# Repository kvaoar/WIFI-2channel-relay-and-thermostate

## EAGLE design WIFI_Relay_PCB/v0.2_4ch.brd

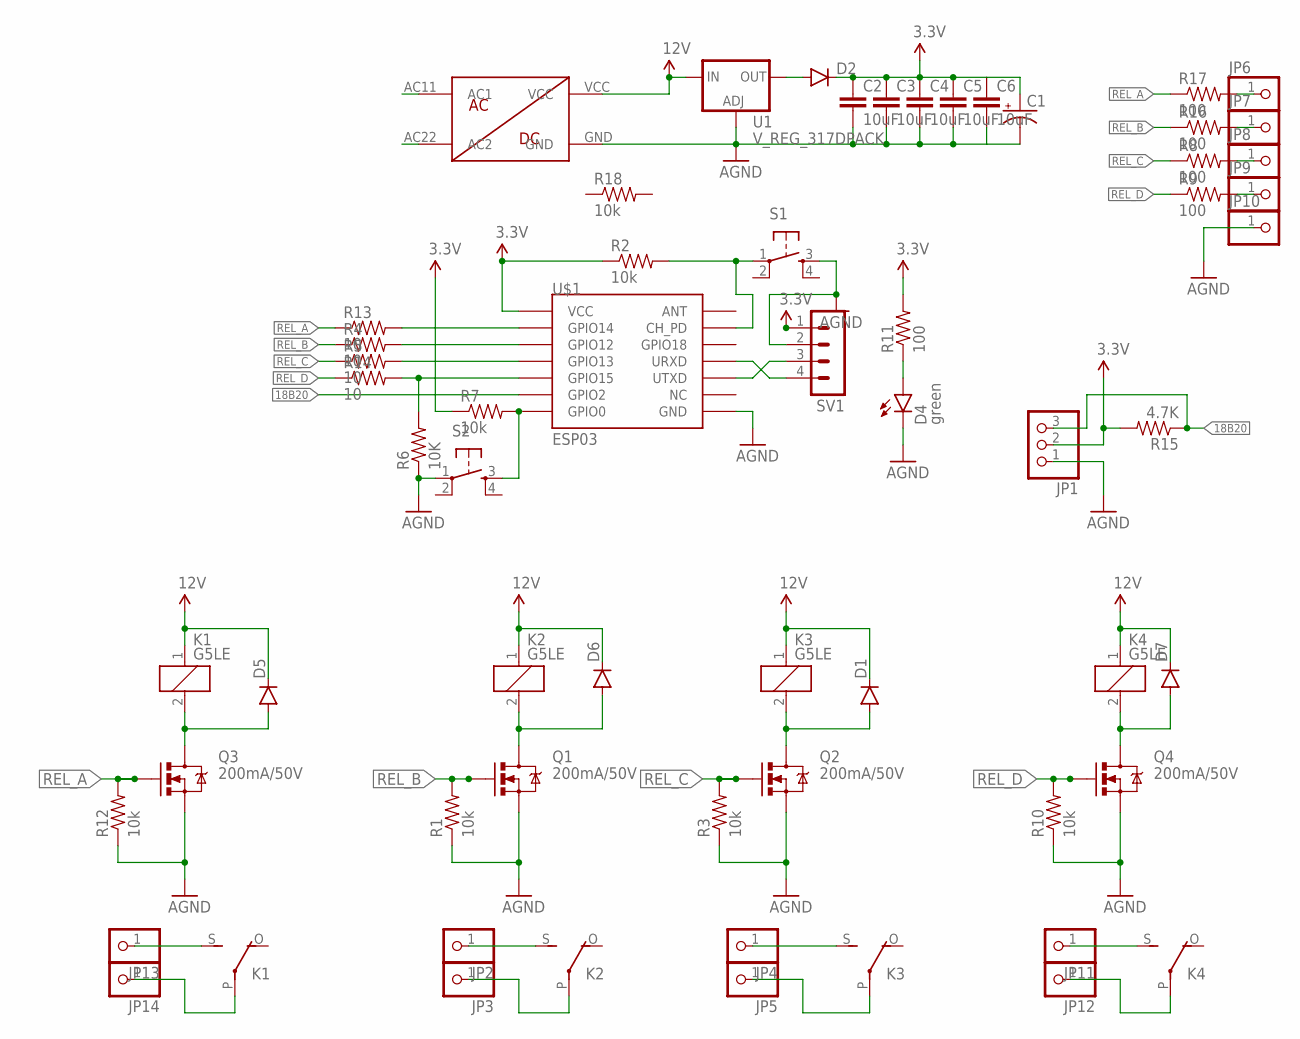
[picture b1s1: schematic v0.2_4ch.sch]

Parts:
C1: CAP_POLPTH3; CPOL-RADIAL-1000UF-63V
C2, C3, C4, C5, C6: 10uF; 0603-CAP
D1, D2, D5, D6, D7: DIODESOD123; SOD-123
D4: green; LED-0603
JP1: PINHD-1X3; 1X03
JP2, JP3, JP4, JP5, JP6, JP7, JP8, JP9, JP10, JP11, JP12, JP13, JP14: PINHD-1X1; 1X01
K1, K2, K3, K4: G5LE
Q1, Q2, Q3, Q4: 200mA/50V; SOT23-3
R1, R2, R3, R7, R10, R12, R18: 10k; 0805
R4, R5, R13, R14: 10; 0805
R6: 10K; 0805
R8, R9, R11, R16, R17: 100; 0805
R15: 4.7K; 0805
S1, S2: TAC_SWITCHPTH; TACTILE-PTH
SV1: MA04-1
U1: V_REG_317DPACK; V-REG_DPACK
U$1: ESP03
U$8: ACDC12V350MA

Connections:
3.3V: C1.1 (+), C2.1, C3.1, C4.1, C5.1, C6.1, D2.C, JP1.2, R2.1, R7.1, R11.2, R15.2, SV1.1, U$1.VCC
12V: D1.C, D5.C, D6.C, D7.C, K1.1, K2.1, K3.1, K4.1, U1.3 (IN), U$8.VCC
18B20: JP1.3, R15.1, U$1.GPIO2
AGND: C1.2 (-), C2.2, C3.2, C4.2, C5.2, C6.2, D4.C, JP1.1, JP10.1, Q1.2 (S), Q2.2 (S), Q3.2 (S), Q4.2 (S), R1.1, R3.1, R6.1, R10.1, R12.1, S1.3, S2.1, SV1.2, U1.1 (ADJ), U$1.GND, U$8.GND
unnamed: SV1.3, U$1.UTXD
unnamed: SV1.4, U$1.URXD
unnamed: D5.A, K1.2, Q3.3 (D)
unnamed: R2.2, S1.1, U$1.CH_PD
unnamed: R4.2, U$1.GPIO12
unnamed: R5.2, U$1.GPIO13
unnamed: R6.2, R14.2, U$1.GPIO15
unnamed: JP8.1, R8.2
unnamed: JP9.1, R9.2
unnamed: R7.2, S2.3, U$1.GPIO0
unnamed: D4.A, R11.1
unnamed: D6.A, K2.2, Q1.3 (D)
unnamed: D7.A, K4.2, Q4.3 (D)
unnamed: D1.A, K3.2, Q2.3 (D)
unnamed: R13.2, U$1.GPIO14
unnamed: JP13.1, K1.S
unnamed: JP14.1, K1.P
unnamed: JP12.1, K4.P
unnamed: JP11.1, K4.S
unnamed: JP5.1, K3.P
unnamed: JP4.1, K3.S
unnamed: JP2.1, K2.S
unnamed: JP3.1, K2.P
unnamed: JP7.1, R16.2
unnamed: JP6.1, R17.2
unnamed: D2.A, U1.4 (OUT)
REL_A: Q3.1 (G), R12.2, R13.1, R17.1
REL_B: Q1.1 (G), R1.2, R4.1, R16.1
REL_C: Q2.1 (G), R3.2, R5.1, R8.1
REL_D: Q4.1 (G), R9.1, R10.2, R14.1

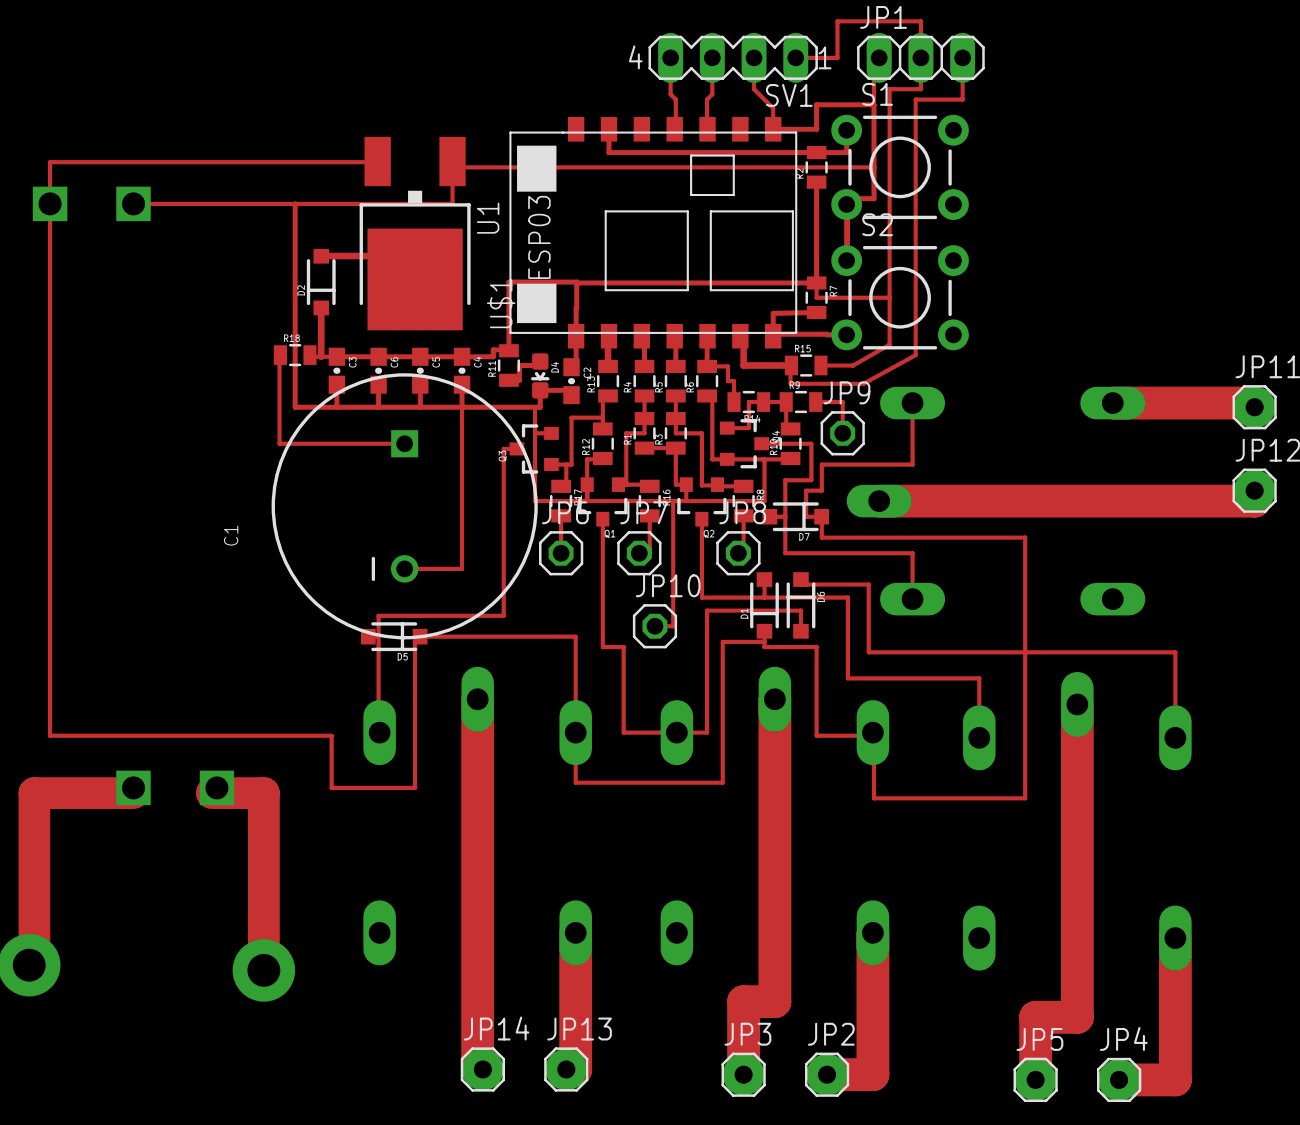
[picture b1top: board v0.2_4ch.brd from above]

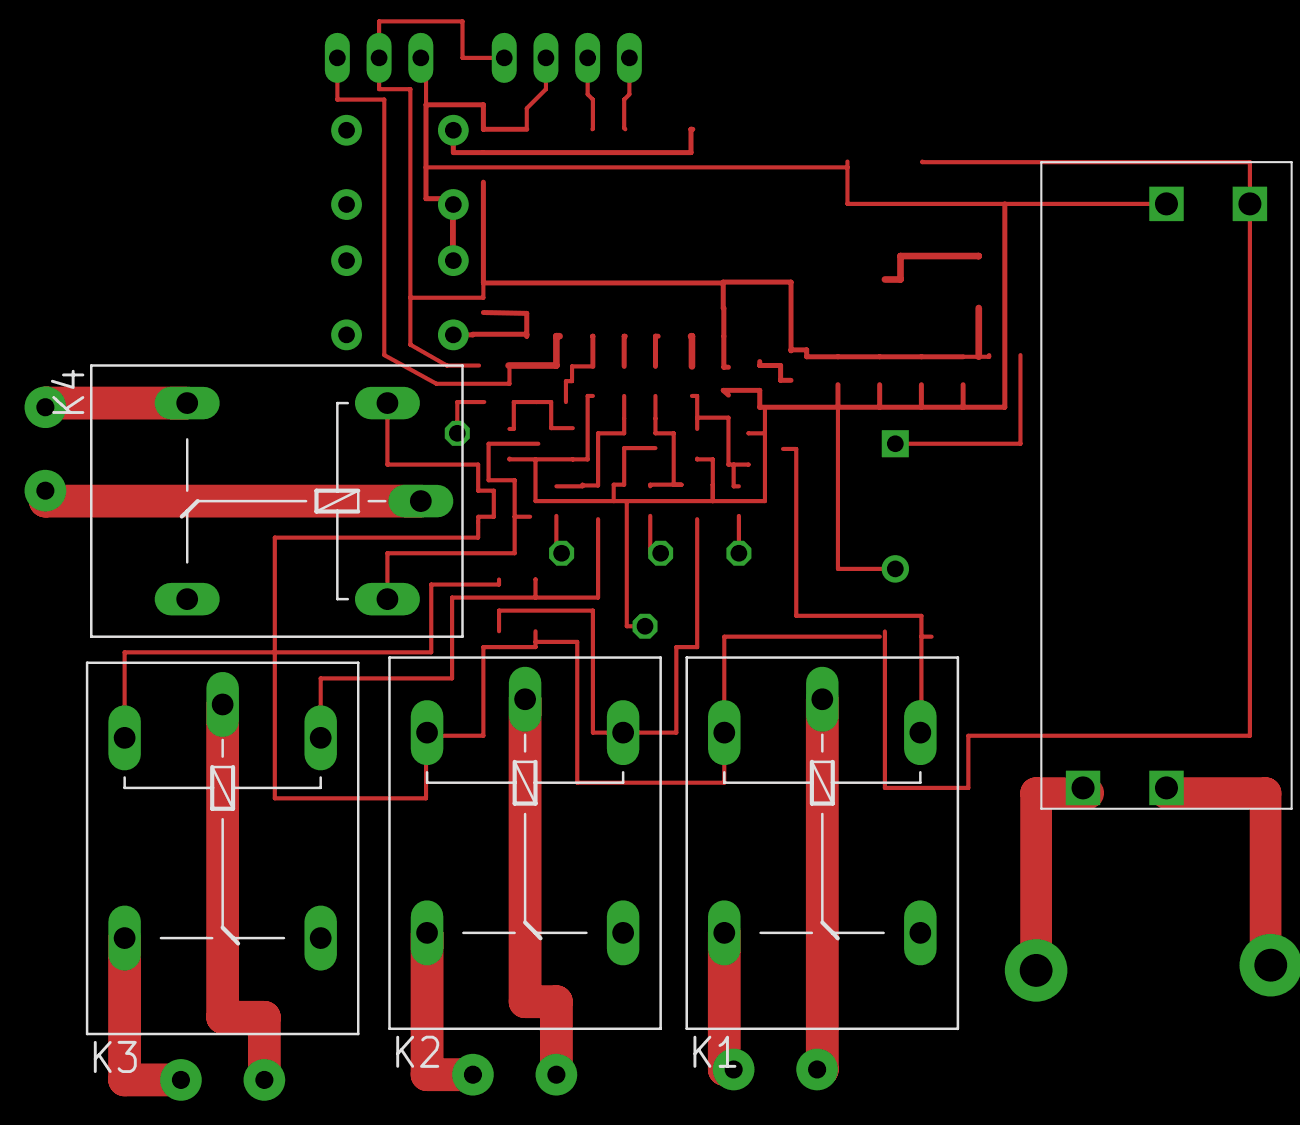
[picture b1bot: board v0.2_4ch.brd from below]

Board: 2 copper layers, 58 parts (5 on the bottom side), 34 nets.

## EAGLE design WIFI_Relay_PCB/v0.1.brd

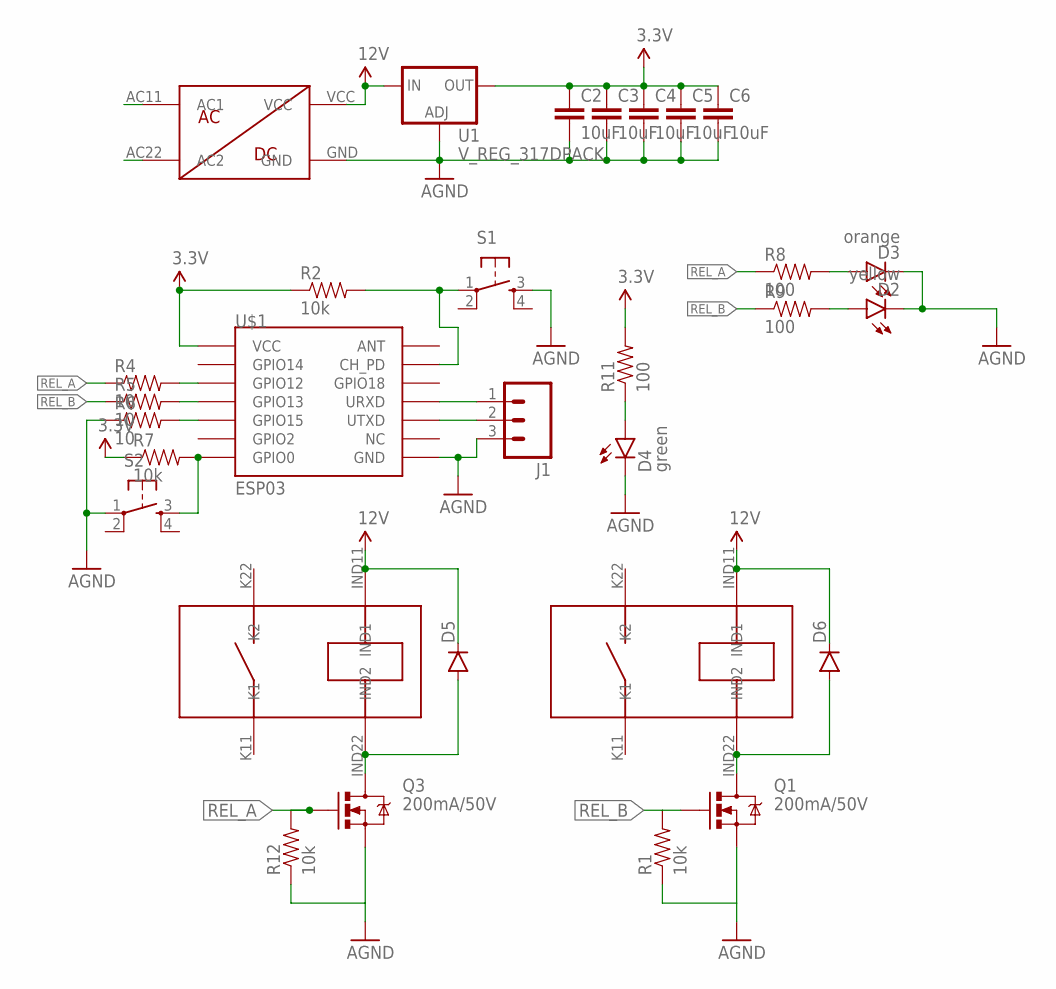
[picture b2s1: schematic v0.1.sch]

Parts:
C2, C3, C4, C5, C6: 10uF; 0603-CAP
D2: yellow; LED-0603
D3: orange; LED-0603
D4: green; LED-0603
D5, D6: DIODESOD123; SOD-123
J1: M03LONGPADS; 1X03_LONGPADS
Q1, Q3: 200mA/50V; SOT23-3
R1, R2, R7, R12: 10k; 0805
R4, R5, R6: 10; 0805
R8, R9, R11: 100; 0805
S1, S2: TAC_SWITCHPTH; TACTILE-PTH
U1: V_REG_317DPACK; V-REG_DPACK
U$1: ESP03
U$8: ACDC12V350MA
U$9, U$10: 302WP

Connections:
3.3V: C2.1, C3.1, C4.1, C5.1, C6.1, R2.1, R7.1, R11.2, U1.4 (OUT), U$1.VCC
12V: D5.C, D6.C, U1.3 (IN), U$8.VCC, U$9.IND11 (IND1), U$10.IND11 (IND1)
AGND: C2.2, C3.2, C4.2, C5.2, C6.2, D2.C, D3.C, D4.C, J1.3, Q1.2 (S), Q3.2 (S), R1.1, R6.1, R12.1, S1.3, S2.1, U1.1 (ADJ), U$1.GND, U$8.GND
unnamed: J1.1, U$1.URXD
unnamed: J1.2, U$1.UTXD
unnamed: D5.A, Q3.3 (D), U$10.IND22 (IND2)
unnamed: R2.2, S1.1, U$1.CH_PD
unnamed: R4.2, U$1.GPIO12
unnamed: R5.2, U$1.GPIO13
unnamed: R6.2, U$1.GPIO15
unnamed: D3.A, R8.2
unnamed: D2.A, R9.2
unnamed: R7.2, S2.3, U$1.GPIO0
unnamed: D4.A, R11.1
unnamed: D6.A, Q1.3 (D), U$9.IND22 (IND2)
REL_A: Q3.1 (G), R4.1, R8.1, R12.2
REL_B: Q1.1 (G), R1.2, R5.1, R9.1

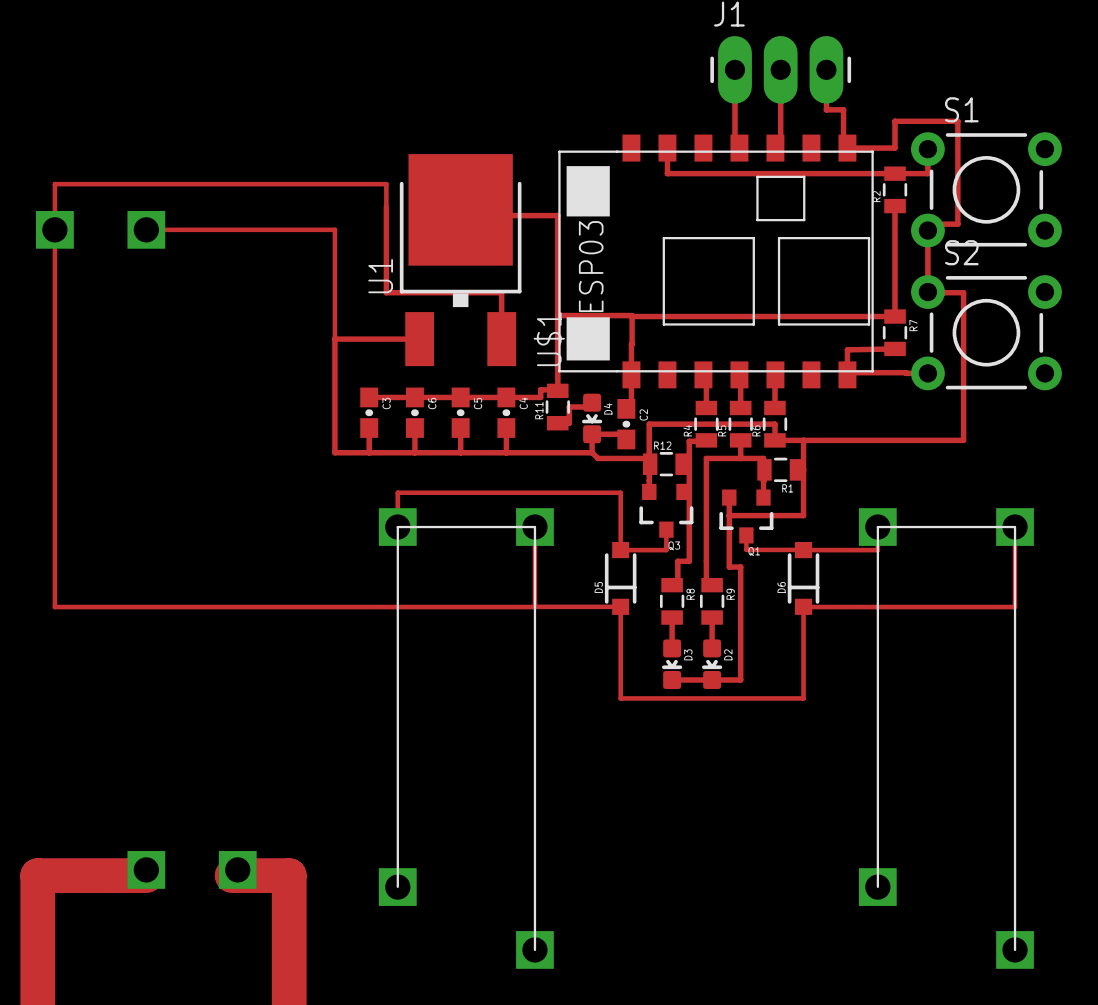
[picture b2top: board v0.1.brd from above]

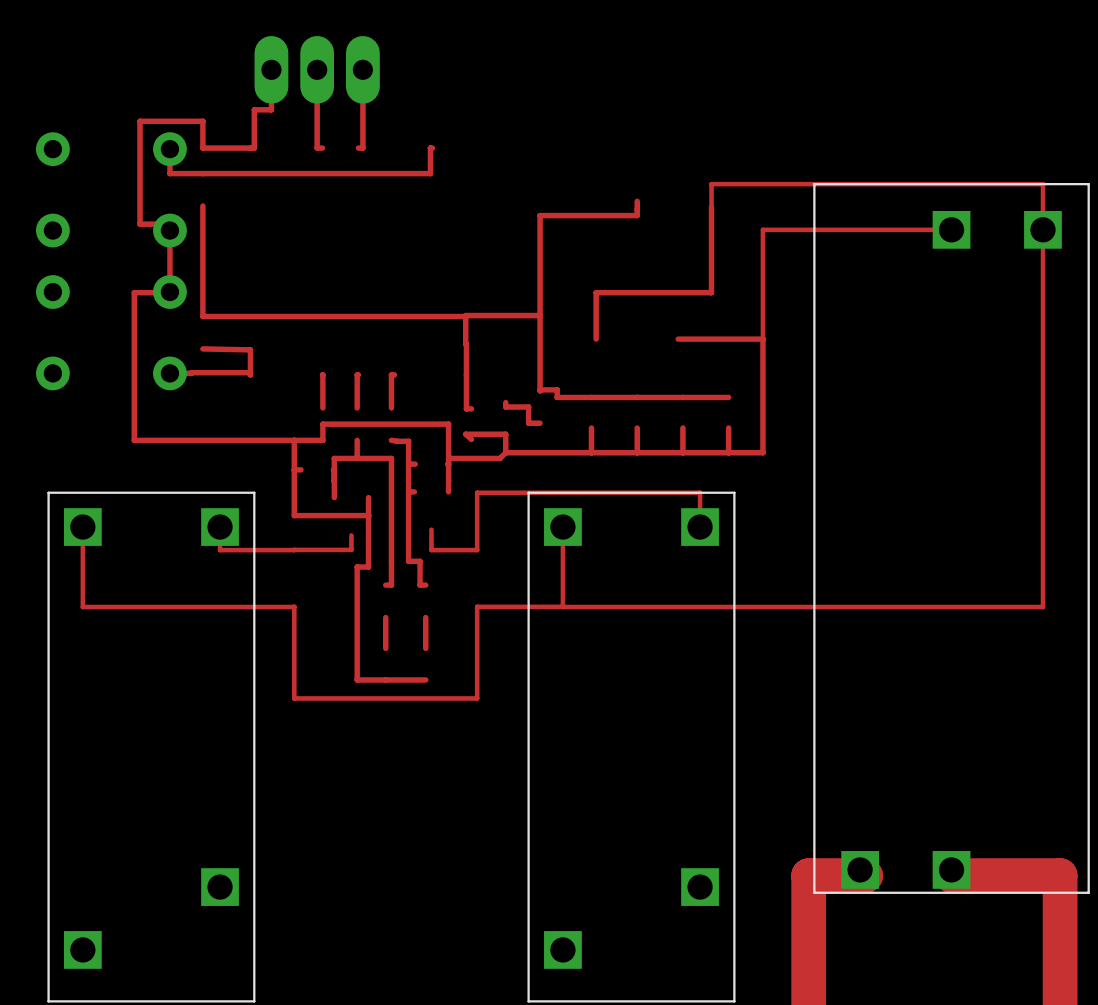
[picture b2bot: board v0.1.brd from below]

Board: 2 copper layers, 30 parts (3 on the bottom side), 17 nets.

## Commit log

2016-09-18 ESP8266 UPD
2016-09-18 Final Fix esp8266 script
2016-09-18 //test

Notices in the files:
parts and their libraries:
SparkFun-Passives: Licensing: Creative Commons ShareAlike 4.0 International - https://creativecommons.org/licenses/by-sa/4.0
